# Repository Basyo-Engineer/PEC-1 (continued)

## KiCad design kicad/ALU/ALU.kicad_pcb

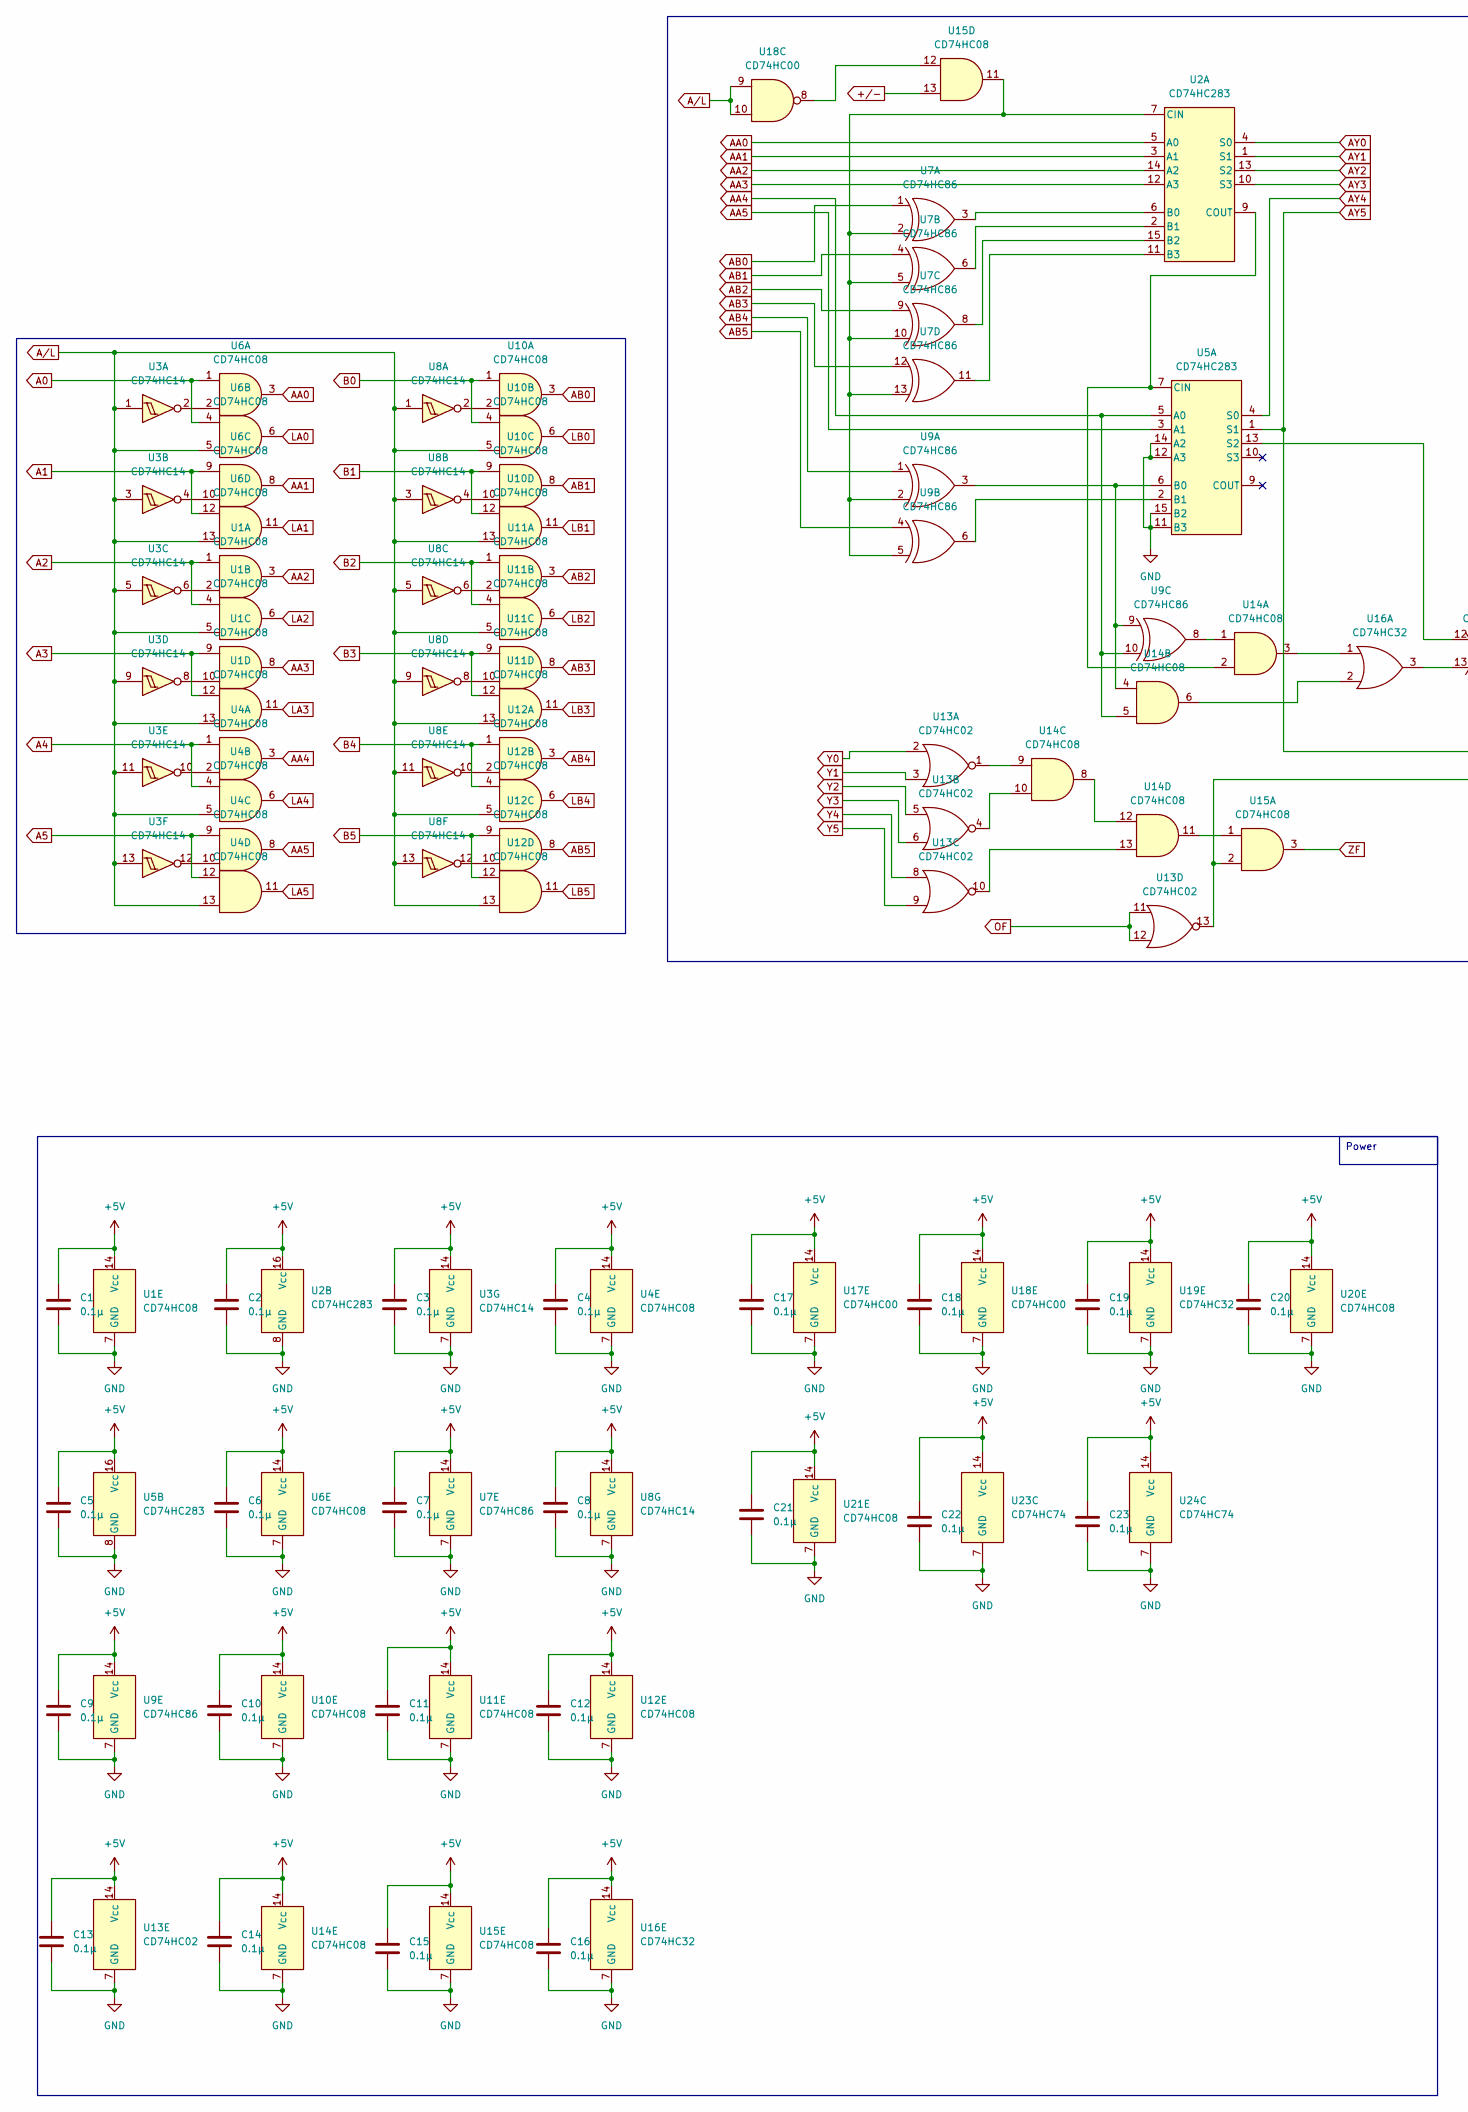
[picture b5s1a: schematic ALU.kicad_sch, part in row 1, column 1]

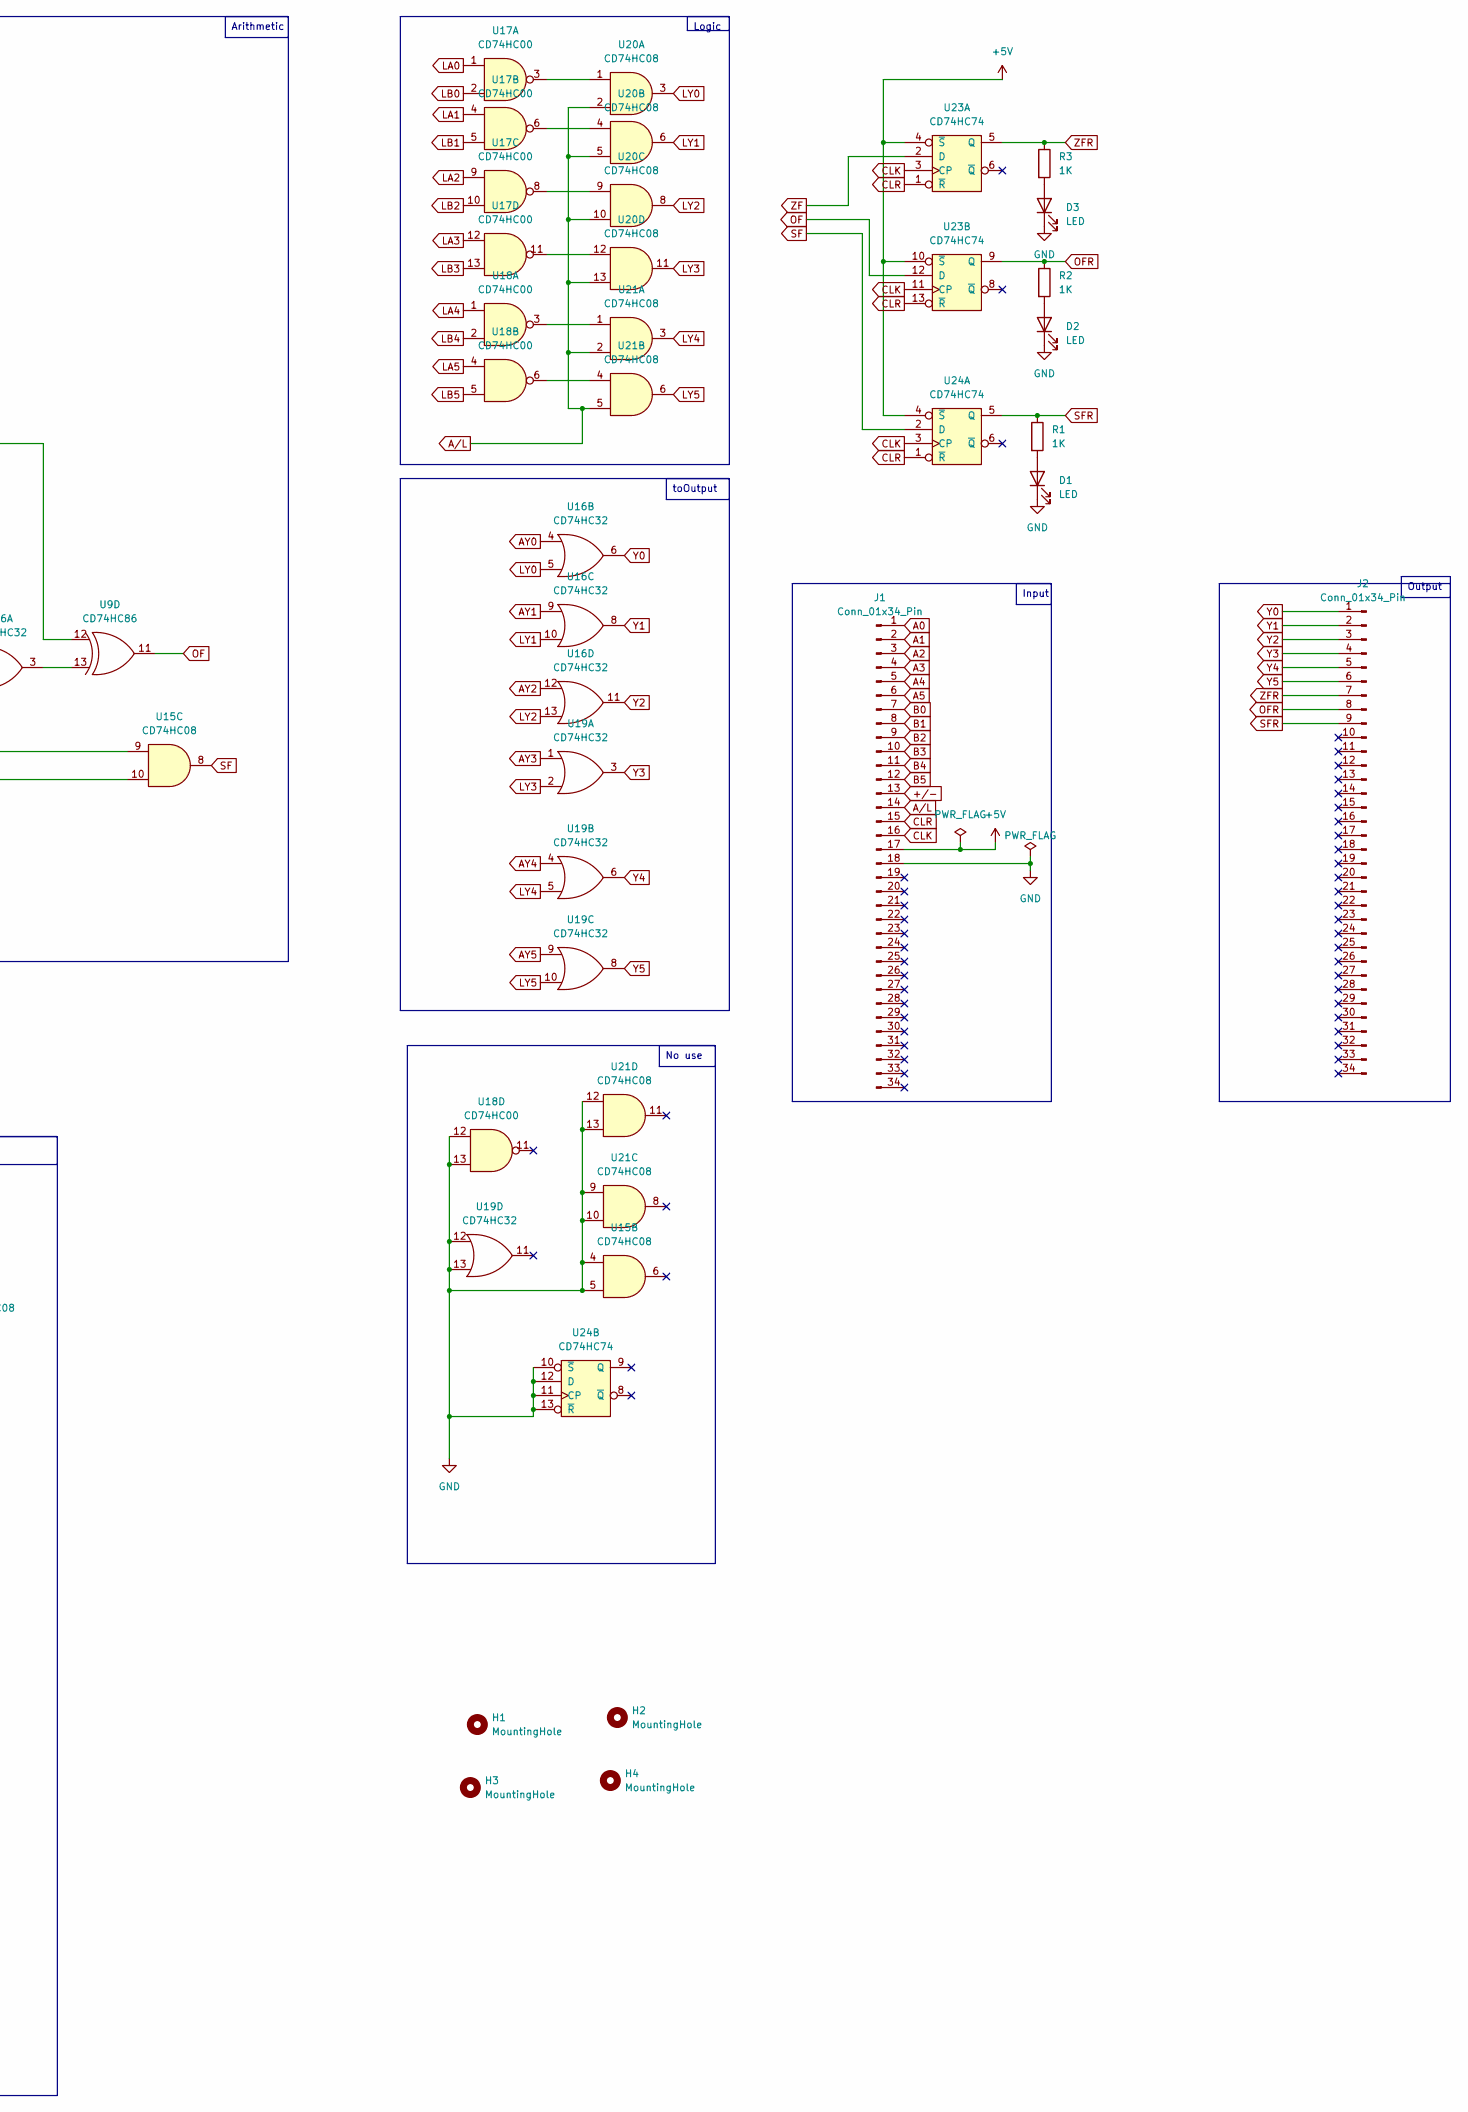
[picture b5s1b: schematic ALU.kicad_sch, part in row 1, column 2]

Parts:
C1, C2, C3, C4, C5, C6, C7, C8, C9, C10, C11, C12, C13, C14, C15, C16, C17, C18, C19, C20, C21, C22, C23: 0.1μ; C_Disc_D5.0mm_W2.5mm_P2.50mm
D1, D2, D3: LED; LED_D3.0mm
H1, H2, H3, H4: MountingHole; MountingHole_3.2mm_M3
J1, J2: Conn_01x34_Pin; PinHeader_2x17_P2.54mm_Horizontal
R1, R2, R3: 1K; R_Axial_DIN0207_L6.3mm_D2.5mm_P10.16mm_Horizontal
U1, U4, U6, U10, U11, U12, U14, U15, U20, U21: CD74HC08; DIP-14_W7.62mm_Socket
U2, U5: CD74HC283; DIP-16_W7.62mm_Socket
U3, U8: CD74HC14; DIP-14_W7.62mm_Socket
U7, U9: CD74HC86; DIP-14_W7.62mm_Socket
U13: CD74HC02; DIP-14_W7.62mm_Socket
U16, U19: CD74HC32; DIP-14_W7.62mm_Socket
U17, U18: CD74HC00; DIP-14_W7.62mm_Socket
U23, U24: CD74HC74; DIP-14_W7.62mm_Socket

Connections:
+5V: C1.1, C2.1, C3.1, C4.1, C5.1, C6.1, C7.1, C8.1, C9.1, C10.1, C11.1, C12.1, C13.1, C14.1, C15.1, C16.1, C17.1, C18.1, C19.1, C20.1, C21.1, C22.1, C23.1, J1.17, U1.14 (Vcc), U2.16 (Vcc), U3.14 (Vcc), U4.14 (Vcc), U5.16 (Vcc), U6.14 (Vcc), U7.14 (Vcc), U8.14 (Vcc), U9.14 (Vcc), U10.14 (Vcc), U11.14 (Vcc), U12.14 (Vcc), U13.14 (Vcc), U14.14 (Vcc), U15.14 (Vcc), U16.14 (Vcc), U17.14 (Vcc), U18.14 (Vcc), U19.14 (Vcc), U20.14 (Vcc), U21.14 (Vcc), U23.4 (~S), U23.10 (~S), U23.14 (Vcc), U24.4 (~S), U24.14 (Vcc)
+/-: J1.13, U15.13
A0: J1.1, U6.1, U6.4
A1: J1.2, U6.9, U6.12
A2: J1.3, U1.1, U1.4
A3: J1.4, U1.9, U1.12
A4: J1.5, U4.1, U4.4
A5: J1.6, U4.9, U4.12
AA0: U2.5 (A0), U6.3
AA1: U2.3 (A1), U6.8
AA2: U1.3, U2.14 (A2)
AA3: U1.8, U2.12 (A3)
AA4: U4.3, U5.5 (A0), U9.10, U14.5
AA5: U4.8, U5.3 (A1)
AB0: U7.1, U10.3
AB1: U7.4, U10.8
AB2: U7.9, U11.3
AB3: U7.12, U11.8
AB4: U9.1, U12.3
AB5: U9.4, U12.8
AY0: U2.4 (S0), U16.4
AY1: U2.1 (S1), U16.9
AY2: U2.13 (S2), U16.12
AY3: U2.10 (S3), U19.1
AY4: U5.4 (S0), U19.4
AY5: U5.1 (S1), U15.9, U19.9
A/L: J1.14, U1.5, U1.13, U3.1, U3.3, U3.5, U3.9, U3.11, U3.13, U4.5, U4.13, U6.5, U6.13, U8.1, U8.3, U8.5, U8.9, U8.11, U8.13, U10.5, U10.13, U11.5, U11.13, U12.5, U12.13, U18.9, U18.10, U20.2, U20.5, U20.10, U20.13, U21.2, U21.5
B0: J1.7, U10.1, U10.4
B1: J1.8, U10.9, U10.12
B2: J1.9, U11.1, U11.4
B3: J1.10, U11.9, U11.12
B4: J1.11, U12.1, U12.4
B5: J1.12, U12.9, U12.12
CLK: J1.16, U23.3 (CP), U23.11 (CP), U24.3 (CP)
CLR: J1.15, U23.1 (~R), U23.13 (~R), U24.1 (~R)
GND: C1.2, C2.2, C3.2, C4.2, C5.2, C6.2, C7.2, C8.2, C9.2, C10.2, C11.2, C12.2, C13.2, C14.2, C15.2, C16.2, C17.2, C18.2, C19.2, C20.2, C21.2, C22.2, C23.2, D1.1 (K), D2.1 (K), D3.1 (K), J1.18, U1.7 (GND), U2.8 (GND), U3.7 (GND), U4.7 (GND), U5.8 (GND), U5.11 (B3), U5.12 (A3), U5.14 (A2), U5.15 (B2), U6.7 (GND), U7.7 (GND), U8.7 (GND), U9.7 (GND), U10.7 (GND), U11.7 (GND), U12.7 (GND), U13.7 (GND), U14.7 (GND), U15.4, U15.5, U15.7 (GND), U16.7 (GND), U17.7 (GND), U18.7 (GND), U18.12, U18.13, U19.7 (GND), U19.12, U19.13, U20.7 (GND), U21.7 (GND), U21.9, U21.10, U21.12, U21.13, U23.7 (GND), U24.7 (GND), U24.10 (~S), U24.11 (CP), U24.12 (D), U24.13 (~R)
LA0: U6.6, U17.1
LA1: U6.11, U17.4
LA2: U1.6, U17.9
LA3: U1.11, U17.12
LA4: U4.6, U18.1
LA5: U4.11, U18.4
LB0: U10.6, U17.2
LB1: U10.11, U17.5
LB2: U11.6, U17.10
LB3: U11.11, U17.13
LB4: U12.6, U18.2
LB5: U12.11, U18.5
LY0: U16.5, U20.3
LY1: U16.10, U20.6
LY2: U16.13, U20.8
LY3: U19.2, U20.11
LY4: U19.5, U21.3
LY5: U19.10, U21.6
unnamed: D1.2 (A), R1.2
unnamed: D2.2 (A), R2.2
unnamed: D3.2 (A), R3.2
unnamed: U1.2, U3.6
unnamed: U1.10, U3.8
unnamed: U2.6 (B0), U7.3
unnamed: U2.2 (B1), U7.6
unnamed: U2.15 (B2), U7.8
unnamed: U2.11 (B3), U7.11
unnamed: U2.7 (CIN), U7.2, U7.5, U7.10, U7.13, U9.2, U9.5, U15.11
unnamed: U2.9 (COUT), U5.7 (CIN), U14.2
unnamed: U3.2, U6.2
unnamed: U3.4, U6.10
unnamed: U3.10, U4.2
unnamed: U3.12, U4.10
unnamed: U5.6 (B0), U9.3, U9.9, U14.4
unnamed: U5.2 (B1), U9.6
unnamed: U5.13 (S2), U9.12
unnamed: U8.2, U10.2
unnamed: U8.4, U10.10
unnamed: U8.6, U11.2
unnamed: U8.8, U11.10
unnamed: U8.10, U12.2
unnamed: U8.12, U12.10
unnamed: U13.1, U14.9
unnamed: U13.4, U14.10
unnamed: U13.10, U14.13
unnamed: U13.13, U15.2, U15.10
unnamed: U9.8, U14.1
unnamed: U14.3, U16.1
unnamed: U14.6, U16.2
unnamed: U14.11, U15.1
unnamed: U14.8, U14.12
unnamed: U15.12, U18.8
unnamed: U9.13, U16.3
unnamed: U17.3, U20.1
unnamed: U17.6, U20.4
unnamed: U17.8, U20.9
unnamed: U17.11, U20.12
unnamed: U18.3, U21.1
unnamed: U18.6, U21.4
OF: U9.11, U13.11, U13.12, U23.12 (D)
OFR: J2.8, R2.1, U23.9 (Q)
SF: U15.8, U24.2 (D)
SFR: J2.9, R1.1, U24.5 (Q)
Y0: J2.1, U13.2, U16.6
Y1: J2.2, U13.3, U16.8
Y2: J2.3, U13.5, U16.11
Y3: J2.4, U13.6, U19.3
Y4: J2.5, U13.8, U19.6
Y5: J2.6, U13.9, U19.8
ZF: U15.3, U23.2 (D)
ZFR: J2.7, R3.1, U23.5 (Q)

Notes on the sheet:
Output
Arithmetic
Input
toOutput
No use
Logic
Power

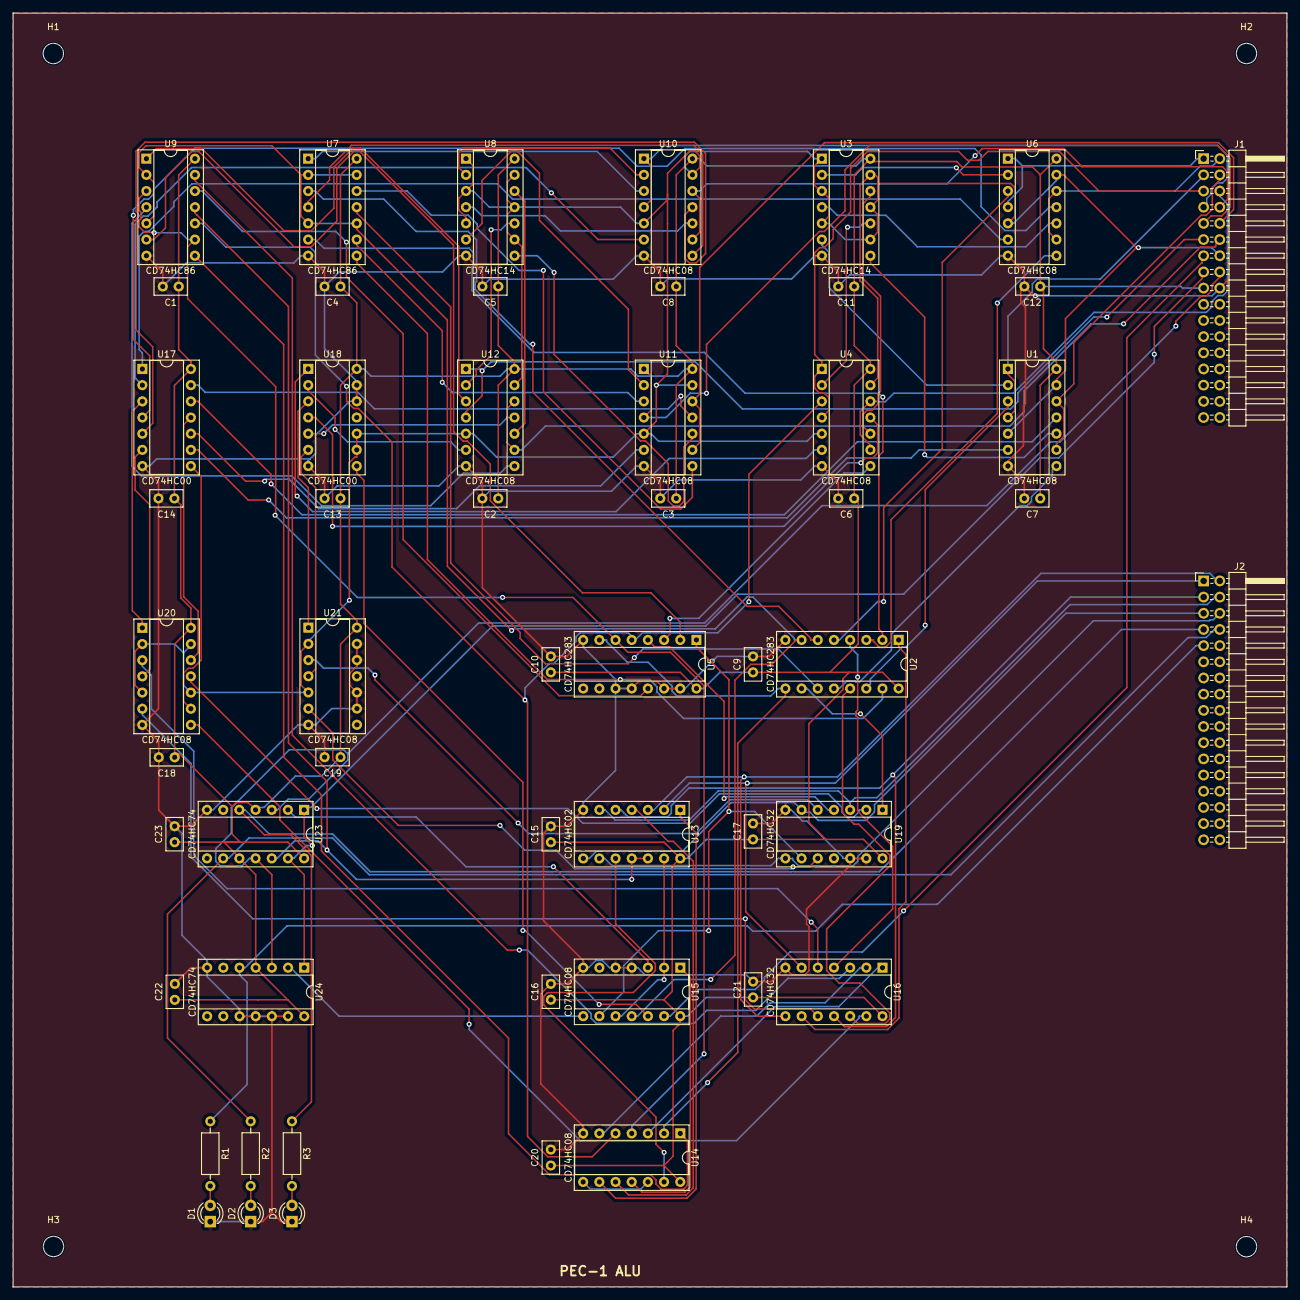
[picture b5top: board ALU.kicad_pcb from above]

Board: 2 copper layers, 200.0 x 200.0 mm, 58 parts (0 on the bottom side), 107 nets.

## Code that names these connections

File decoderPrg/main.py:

from machine import Pin
import time


oc3 = machine.Pin(1, machine.Pin.IN)
oc2 = machine.Pin(2, machine.Pin.IN)
oc1 = machine.Pin(3, machine.Pin.IN)
oc0 = machine.Pin(4, machine.Pin.IN)

ol3 = machine.Pin(5, machine.Pin.IN)
ol2 = machine.Pin(6, machine.Pin.IN)
ol1 = machine.Pin(7, machine.Pin.IN)
ol0 = machine.Pin(8, machine.Pin.IN)

zf = machine.Pin(9, machine.Pin.IN)
of = machine.Pin(10, machine.Pin.IN)
sf = machine.Pin(11, machine.Pin.IN)

sela2 = machine.Pin(14, machine.Pin.OUT)
sela1 = machine.Pin(13, machine.Pin.OUT)
sela0 = machine.Pin(12, machine.Pin.OUT)
selb2 = machine.Pin(17, machine.Pin.OUT)
selb1 = machine.Pin(16, machine.Pin.OUT)
selb0 = machine.Pin(15, machine.Pin.OUT)

ld0 = machine.Pin(18, machine.Pin.OUT)
ld1 = machine.Pin(19, machine.Pin.OUT)
ld2 = machine.Pin(20, machine.Pin.OUT)
ld3 = machine.Pin(21, machine.Pin.OUT)
ldo = machine.Pin(22, machine.Pin.OUT)
ldpc = machine.Pin(26, machine.Pin.OUT)

pm = machine.Pin(27, machine.Pin.OUT)
al = machine.Pin(28, machine.Pin.OUT)

oc = [0, 0, 0, 0]
ol = [0, 0, 0, 0]
flag = [0, 0, 0]

selector = [0, 0, 0, 0, 0, 0]
Load = [1, 1, 1, 1, 1, 1]


alithm = [0, 0]




mov1 = [0, 0, 1, 0]
mov2 = [0, 0, 1, 1]
add1 = [0, 1, 0, 0]
add2 = [0, 1, 0, 1]
sub1 = [0, 1, 1, 0]
sub2 = [0, 1, 1, 1]
nan1 = [1, 0, 0, 0]
nan2 = [1, 0, 0, 1]

jmp =  [0, 0, 0, 1]
jno =  [1, 0, 1, 1]
jze =  [1, 0, 1, 0]
jmi =  [1, 1, 0, 0]
jpl =  [1, 1, 0, 1]
inp =  [1, 1, 1, 0]
outp = [1, 1, 1, 1]
nop =  [0, 0, 0, 0]



def decoder (opeland):
    ret = [1, 1, 1, 1, 1, 1]
    
    if(opeland[0] == 0 and opeland[1] == 0):
        ret[0] = 0
        
    if(opeland[0] == 0 and opeland[1] == 1):
        ret[1] = 0
        
    if(opeland[0] == 1 and opeland[1] == 0):
        ret[2] = 0

    if(opeland[0] == 1 and opeland[1] == 1):
        ret[3] = 0
    
    return ret

while True:
    oc[0] = oc3.value()
    oc[1] = oc2.value()
    oc[2] = oc1.value()
    oc[3] = oc0.value()

    ol[0] = ol3.value()
    ol[1] = ol2.value()
    ol[2] = ol1.value()
    ol[3] = ol0.value()

    flag[0] = zf.value()
    flag[1] = of.value()
    flag[2] = sf.value()

    
    if oc == mov1:
        selector = [0, ol[2], ol[3], 1, 1, 0]
        Load = decoder(ol)
        alithm = [0, 0]
        print(oc)
        print(ol)
        print(flag)
        print("mov1")
        
    if oc == mov2:
        selector = [1, 0, 1, 1, 1, 0]
        Load = decoder(ol)
        alithm = [0, 0]
        print(oc)
        print(ol)
        print(flag)
        print("mov2")
        
    if oc == add1:
        selector = [0, ol[0], ol[1], 0, ol[2], ol[3]]
        Load = decoder(ol)
        alithm = [0, 0]
        print(oc)
        print(ol)
        print(flag)
        print("add1")
        
    if oc == add2:
        selector = [0, ol[0], ol[1], 1, 0, 1]
        Load = decoder(ol)
        alithm = [0, 0]
        print(oc)
        print(ol)
        print(flag)
        print("add2")
        
    if oc == sub1:
        selector = [0, ol[0], ol[1], 0, ol[2], ol[3]]
        Load = decoder(ol)
        alithm = [1, 0]
        print(oc)
        print(ol)
        print(flag)
        print("sub1")
        
    if oc == sub2:
        selector = [0, ol[0], ol[1], 1, 0, 1]
        Load = decoder(ol)
        alithm = [1, 0]
        print(oc)
        print(ol)
        print(flag)
        print("sub2")
        
    if oc == nan1:
        selector = [0, ol[0], ol[1], 0, ol[2], ol[3]]
        Load = decoder(ol)
        alithm = [0, 1]
        print(oc)
        print(ol)
        print(flag)
        print("nan1")
        
    if oc == nan2:
        selector = [0, ol[0], ol[1], 1, 0, 1]
        Load = decoder(ol)
        alithm = [0, 1]
        print(oc)
        print(ol)
        print(flag)
        print("nan2")
        
    if oc == jmp:
        selector = [1, 0, 1, 1, 1, 0]
        Load = [1, 1, 1, 1, 1, 0]
        alithm = [0, 0]
        print(oc)
        print(ol)
        print(flag)
        print("jmp")
        
    if oc == jno and flag[1] == 0:
        selector = [1, 0, 1, 1, 1, 0]
        Load = [1, 1, 1, 1, 1, 0]
        alithm = [0, 0]
        print(oc)
        print(ol)
        print(flag)
        print("jno")
        
    if oc == jze and flag[0] == 1:
        selector = [1, 0, 1, 1, 1, 0]
        Load = [1, 1, 1, 1, 1, 0]
        alithm = [0, 0]
        print(oc)
        print(ol)
        print(flag)
        print("jze")
    elif oc == jze and flag[0] == 0:
        selector = [1, 1, 0, 1, 1, 0]
        Load = [1, 1, 1, 1, 1, 1]
        alithm = [0, 0]
        
    if oc == jmi and flag[2] == 1:
        selector = [1, 0, 1, 1, 1, 0]
        Load = [1, 1, 1, 1, 1, 0]
        alithm = [0, 0]
        print(oc)
        print(ol)
        print(flag)
        print("jmi")
        
    if oc == jpl and flag[0] == 0 and flag[2] == 0:
        selector = [1, 0, 1, 1, 1, 0]
        Load = [1, 1, 1, 1, 1, 0]
        alithm = [0, 0]
        print(oc)
        print(ol)
        print(flag)
        print("jpl")
        
    if oc == inp:
        selector = [1, 0, 0, 1, 1, 0]
        Load = decoder(ol)
        alithm = [0, 0]
        print(oc)
        print(ol)
        print(flag)
        print("inp")
        
        
    if oc == outp:
        selector = [0, ol[0], ol[1], 1, 1, 0]
        Load = [1, 1, 1, 1, 0, 1]
        alithm = [0, 0]
        print(oc)
        print(ol)
        print(flag)
        print("outp")
        
    if oc == nop:
        selector = [1, 1, 0, 1, 1, 0]
        Load = [1, 1, 1, 1, 1, 1]
        alithm = [0, 0]
        print(oc)
        print(ol)
        print(flag)
        print("nop")
        
    #print(Load)
    
    sela2.value(selector[0])
    sela1.value(selector[1])
    sela0.value(selector[2])
    selb2.value(selector[3])
    selb1.value(selector[4])
    selb0.value(selector[5])
    
    ld0.value(Load[0])
    ld1.value(Load[1])
    ld2.value(Load[2])
    ld3.value(Load[3])
    ldo.value(Load[4])
    ldpc.value(Load[5])
    
    pm.value(alithm[0])
    al.value(alithm[1])
            
        

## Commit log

2023-11-12 Upload File
2023-11-12 Create README.md
    説明書いた
2023-11-12 Update README.md
    誤字修正
2023-11-12 Update README.md
    正式名称の追加
2023-11-12 Discord Bot test
2023-11-12 Update README.md
    Architectureの追加
2023-11-27 Logisim用のシミュレータファイルの追加
2023-11-27 mainとtestのマージ
2023-12-02 デコーダプログラムの修正
